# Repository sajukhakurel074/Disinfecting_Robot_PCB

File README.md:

# Disinfecting_Robot
Main circuit board design for disinfecting Robot Project.

This project was funded by Nepal Academy of Science and Technology (NAST) during the Covid-19 pandemic. The main aim of this project was to use a remotely comtrolled robot that would spary the disinfecting solution in the infected areas.

# Features of the board
1. Simple 4 wheel drive
2. Bluetooth controlled functions
3. Relay switched Water Pump
4. 2-D axis spraying arm 
  - Servo for y-axis
  - Stepper for x-axis
5. Proximity sensor at the edges to avoid collision

# Final Board After Assmebly

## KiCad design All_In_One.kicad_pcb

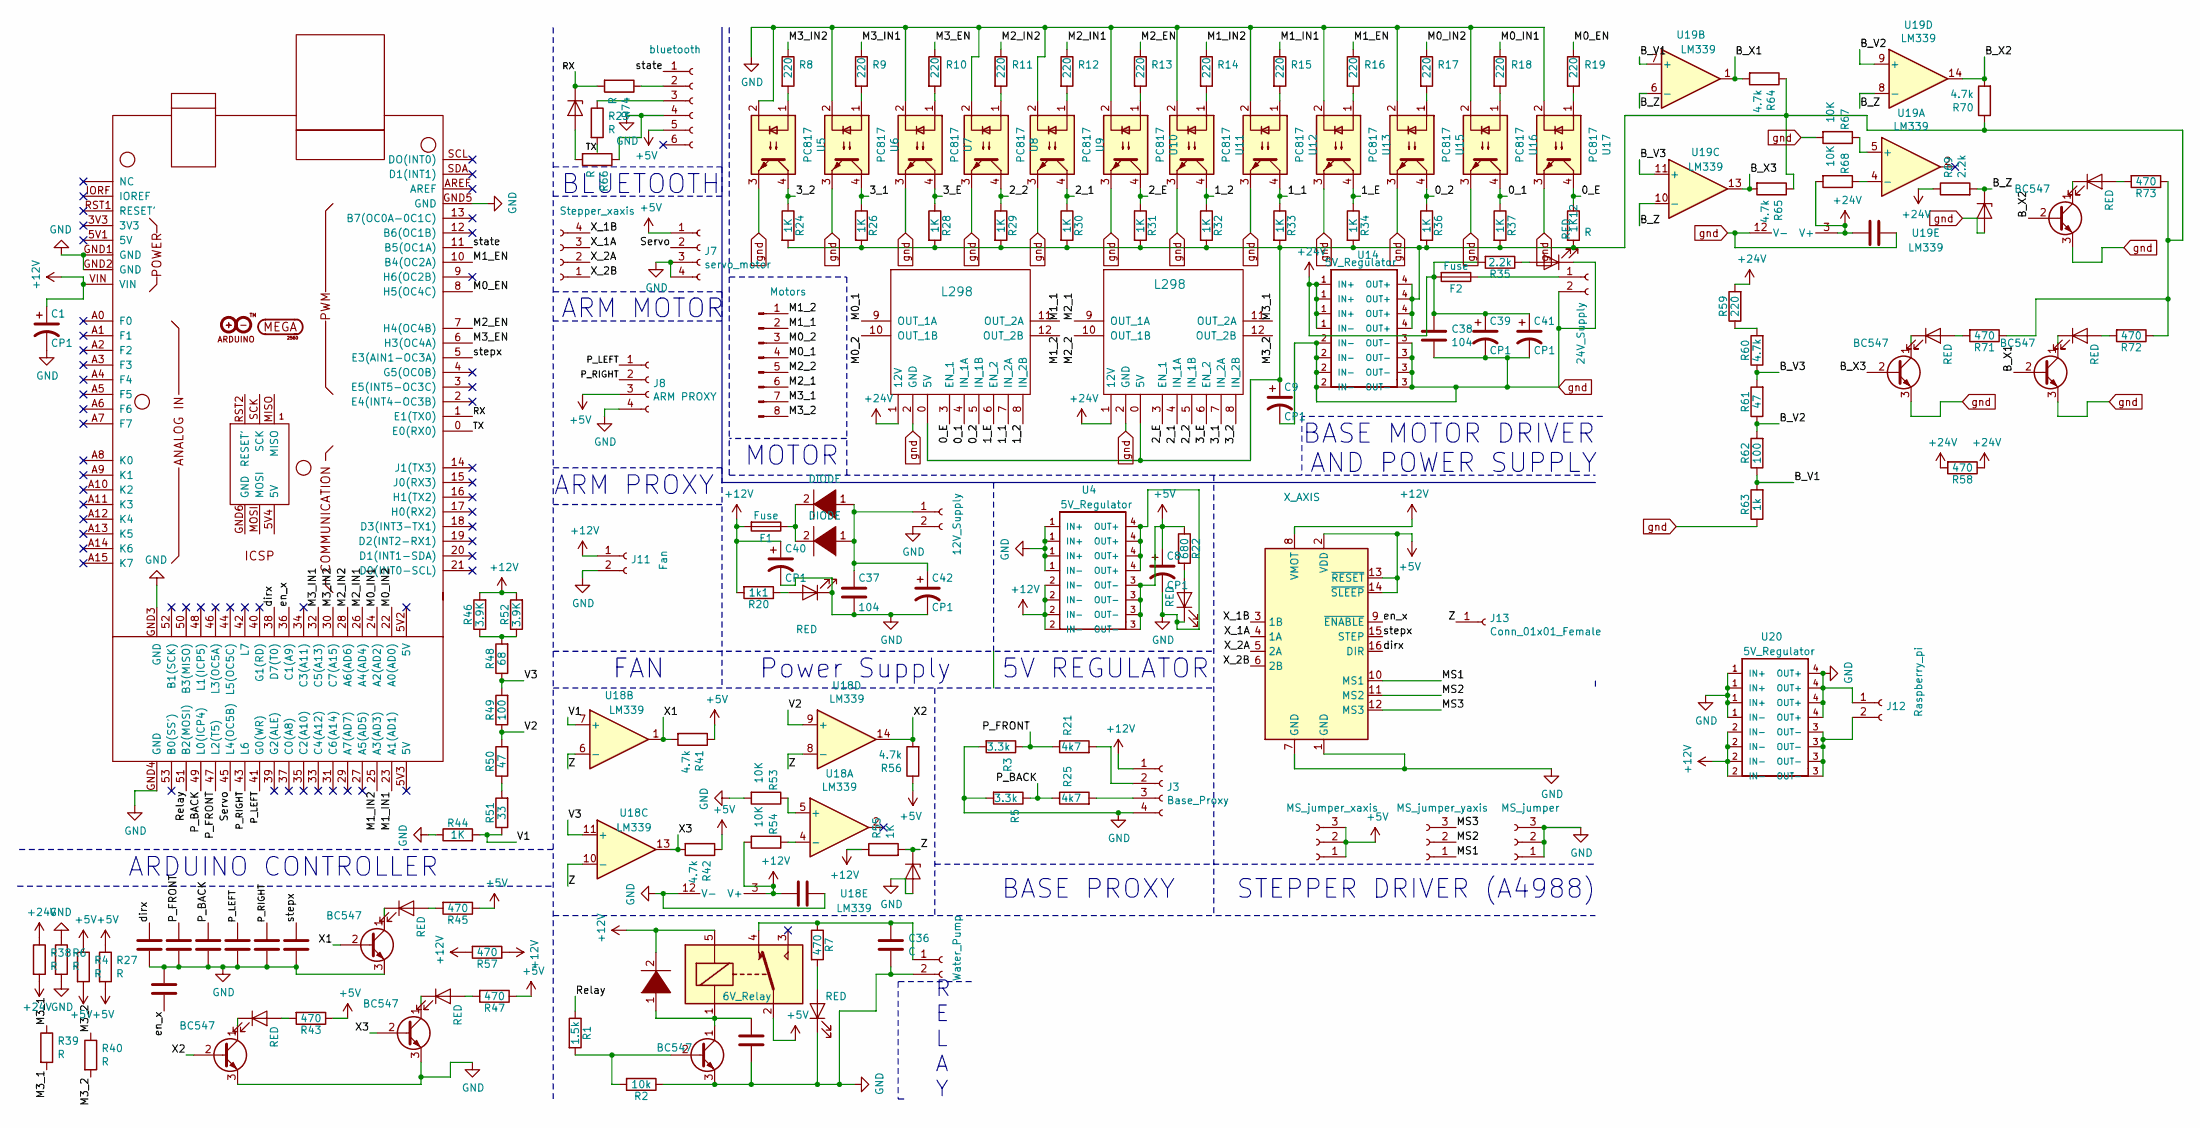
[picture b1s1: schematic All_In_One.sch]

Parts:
1K12: R; Resistor_small
A1: X_AXIS; A4998
C1, C8, C9, C40, C41: CP1; Capacitor_1000uF
C2, C3, C4, C5, C6, C7, C13, C25, C27, C33, C36: C; Capacitor_Disc_Small
C37, C38: 104; Capacitor_Disc_Small
C39, C42: CP1; Capacitor_10uF
D1, D3, D10: DIODE; Diode_Medium
D2, D4, D5, D6, D8, D9, D11, D13, D15, D16: RED; LED_D3.0mm
D7, D12, D14: D_Zener; D_T-1_P5.08mm_Horizontal
F1, F2: Fuse; Fuse_Holder
J1: MS_jumper_xaxis; PinHeader_1x03_P2.54mm_Vertical
J2: MS_jumper_yaxis; PinHeader_1x03_P2.54mm_Vertical
J3: Base_Proxy; New_conn_1x4
J4: Water_Pump; New_conn_1x2
J5: MS_jumper; PinHeader_1x03_P2.54mm_Vertical
J6: Stepper_xaxis; New_conn_1x4
J7: servo_motor; New_conn_1x4
J8: ARM PROXY; New_conn_1x4
J9: bluetooth
J10: Motors; New_conn_1x8
J11: Fan; New_conn_1x2
J12: Raspberry_pi; New_conn_1x2
J13: Conn_01x01_Female; PinHeader_1x01_P2.00mm_Vertical
Q1, Q2, Q3, Q4, Q5, Q6, Q7: BC547
R1: 1.5k; Resistor_small
R2: 10k; Resistor_small
R3, R5: 3.3k; Resistor_small
R4, R6, R23, R27, R38, R39, R40, R66, R74: R; Resistor_small
R7, R43, R45, R47, R57, R58, R71, R72, R73: 470; Resistor_small
R8, R9, R10, R11, R12, R13, R14, R15, R16, R17, R18, R19, R59: 220; Resistor_small
R20: 1k1; Resistor_small
R21, R25: 4k7; Resistor_small
R22: 680; Resistor_small
R24, R26, R28, R29, R30, R31, R32, R33, R34, R36, R37, R44, R55: 1K; Resistor_small
R35, R69: 2.2k; Resistor_small
R41, R42, R56, R60, R64, R65, R70: 4.7k; Resistor_small
R46, R52: 3.9K; Resistor_small
R48: 68; Resistor_small
R49, R62: 100; Resistor_small
R50, R61: 47; Resistor_small
R51: 33; Resistor_small
R53, R54, R67, R68: 10K; Resistor_small
R63: 1k; Resistor_small
Rly1: 6V_Relay; Relay_6V
U1: Prashant_library_Arduino_Mega2560_Shield; Arduino_Mega2560_Shield
U2, U3: L298; saju_____L298
U4, U20: 5V_Regulator; Buck_5A
U5, U6, U7, U8, U9, U10, U11, U12, U13, U15, U16, U17: PC817; DIP-4_W7.62mm
U14: 5V_Regulator; Buck_Regulator
U18, U19: LM339; DIP-14_W7.62mm_LongPads
d1: 12V_Supply; Solar_Connector
d2: 24V_Supply; Solar_Connector

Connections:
+5V: A1.2 (VDD), A1.13 (~RESET), A1.14 (~SLEEP), C8.1, J1.1, J1.2, J1.3, J7.1, J8.3, J9.5, R4.1, R4.2, R22.1, R27.1, R27.2, R41.1, R42.1, R43.1, R45.1, R47.1, R56.1, Rly1.2, U4.3 (OUT-); also elsewhere on the board
+12V: A1.8 (VMOT), C1.1, C4.2, C40.1, D1.2 (A), F1.2, J3.1, J11.1, R20.2, R46.2, R52.2, R54.2, R55.1, R57.1, R57.2, Rly1.5, U1.VIN, U4.2 (IN-), U18.3 (V+), U20.2 (IN-); also elsewhere on the board
+24V: C6.2, C38.1, C39.1, C41.1, F2.2, R35.2, R38.1, R38.2, R58.1, R58.2, R59.2, R68.2, R69.1, U2.1 (12V), U3.1 (12V), U14.1 (IN+), U19.3 (V+)
/0_1: R37.1, U2.4 (IN_1A), U16.4
/0_2: R36.1, U2.5 (IN_1B), U15.4
/0_E: 1K12.1, U2.3 (EN_1), U17.4
/1_1: R33.1, U2.7 (IN_2A), U12.4
/1_2: R32.1, U2.8 (IN_2B), U11.4
/1_E: R34.1, U2.6 (EN_2), U13.4
/2_1: R30.1, U3.4 (IN_1A), U9.4
/2_2: R29.1, U3.5 (IN_1B), U8.4
/2_E: R31.1, U3.3 (EN_1), U10.4
/3_1: R26.1, U3.7 (IN_2A), U6.4
/3_2: R24.1, U3.8 (IN_2B), U5.4
/3_E: R28.1, U3.6 (EN_2), U7.4
/B_V1: R62.1, R63.2, U19.7 (+)
/B_V2: R61.1, R62.2, U19.9 (+)
/B_V3: R60.1, R61.2, U19.11 (+)
/B_X1: Q6.2 (B), R64.2, U19.1
/B_X2: Q7.2 (B), R70.2, U19.14; also elsewhere on the board
/B_X3: Q5.2 (B), R65.2, U19.13
/B_Z: D14.1 (K), R69.2, U19.6 (-), U19.8 (-), U19.10 (-)
/M0_1: J10.4, U2.9 (OUT_1A)
/M0_2: J10.3, U2.10 (OUT_1B)
/M0_EN: R19.1, U1.8 (H5(OC4C))
/M0_IN1: R18.1, U1.24 (A2(AD2))
/M0_IN2: R17.1, U1.22 (A0(AD0))
/M1_1: J10.2, U2.11 (OUT_2A)
/M1_2: J10.1, U2.12 (OUT_2B)
/M1_EN: R16.1, U1.10 (B4(OC2A))
/M1_IN1: R15.1, U1.23 (A1(AD1))
/M1_IN2: R14.1, U1.25 (A3(AD3))
/M2_1: J10.6, U3.9 (OUT_1A)
/M2_2: J10.5, U3.10 (OUT_1B)
/M2_EN: R13.1, U1.7 (H4(OC4B))
/M2_IN1: R12.1, U1.26 (A4(AD4))
/M2_IN2: R11.1, U1.28 (A6(AD6))
/M3_1: J10.7, R39.1, R39.2, U3.11 (OUT_2A)
/M3_2: J10.8, R40.1, R40.2, U3.12 (OUT_2B)
/M3_EN: R10.1, U1.6 (H3(OC4A))
/M3_IN1: R9.1, U1.32 (C5(A13))
/M3_IN2: R8.1, U1.30 (C7(A15))
/MS1: A1.10 (MS1), J2.1; also elsewhere on the board
/MS2: A1.11 (MS2), J2.2; also elsewhere on the board
/MS3: A1.12 (MS3), J2.3; also elsewhere on the board
/P_BACK: C5.1, R5.1, R25.1, U1.49 (L0(ICP4))
/P_FRONT: C2.1, R3.1, R21.1, U1.47 (L2(T5))
/P_LEFT: C25.1, J8.1, U1.41 (G0(WR))
/P_RIGHT: C27.1, J8.2, U1.43 (L6)
/RX: D7.1 (K), R74.2, U1.1 (E1(TX0))
/Relay: R1.1, U1.51 (B2(MOSI))
/Servo: J7.2, U1.45 (L4(OC5B))
/TX: R23.2, U1.0 (E0(RX0))
/V1: R44.2, R51.1, U18.7 (+)
/V2: R49.1, R50.2, U18.9 (+)
/V3: R48.1, R49.2, U18.11 (+)
/X1: Q3.2 (B), R41.2, U18.1
/X2: Q2.2 (B), R56.2, U18.14
/X3: Q4.2 (B), R42.2, U18.13
/X_1A: A1.4 (1A), J6.3
/X_1B: A1.3 (1B), J6.4
/X_2A: A1.5 (2A), J6.2
/X_2B: A1.6 (2B), J6.1
/Z: D12.1 (K), J13.1, R55.2, U18.6 (-), U18.8 (-), U18.10 (-); also elsewhere on the board
/dirx: A1.16 (DIR), C13.1, U1.38 (D7(T0))
/en_x: A1.9 (~ENABLE), C3.1, U1.36 (C1(A9))
/state: J9.1, U1.11 (B5(OC1A))
/stepx: A1.15 (STEP), C33.1, U1.5 (E3(AIN1-OC3A))
GND: A1.1 (GND), A1.7 (GND), C1.2, C2.2, C3.2, C4.1, C5.2, C7.2, C8.2, C13.2, C25.2, C27.2, C33.2, C36.2, C37.2, C40.2, C42.2, D2.1 (K), D9.1 (K), D11.1 (K), D12.2 (A), J3.4, J4.2, J5.1, J5.2, J5.3, J7.3, J7.4, J8.4, J9.4, J11.2, J12.1, Q1.3 (E), Q2.3 (E), Q3.3 (E), Q4.3 (E), R2.1, R3.2, R5.2, R6.1, R6.2, R44.1, R53.2, R66.1, U1.GND1 (GND), U1.GND2 (GND), U1.GND3 (GND), U1.GND4 (GND), U1.GND5 (GND), U4.1 (IN+), U4.4 (OUT+), U5.2, U6.2, U7.2, U8.2, U9.2, U10.2, U11.2, U12.2, U13.2, U15.2, U16.2, U17.2, U18.12 (V-), U20.1 (IN+), U20.4 (OUT+), d1.2; also elsewhere on the board
unnamed 69: 1K12.2, C9.1, R24.2, R26.2, R28.2, R29.2, R30.2, R31.2, R32.2, R33.2, R34.2, R36.2, R37.2, R64.1, R65.1, R70.1, R71.1, R72.1, R73.1, U2.0 (5V), U3.0 (5V), U14.4 (OUT+); also elsewhere on the board
unnamed: C7.1, D1.1 (K), Q1.1 (C), Rly1.1
unnamed: C36.1, J4.1, R7.1, Rly1.4
unnamed 72: C37.1, C42.1, D3.1 (K), D10.1 (K), d1.1; also elsewhere on the board
unnamed: D2.2 (A), R7.2
unnamed: D4.1 (K), Q2.1 (C)
unnamed: D4.2 (A), R43.2
unnamed: D5.1 (K), Q3.1 (C)
unnamed: D5.2 (A), R45.2
unnamed: D6.1 (K), Q4.1 (C)
unnamed: D6.2 (A), R47.2
unnamed: D7.2 (A), R66.2
unnamed: D8.2 (A), R35.1
unnamed: D9.2 (A), R20.1
unnamed: D3.2 (A), D10.2 (A), F1.1
unnamed: D11.2 (A), R22.2
unnamed: D13.1 (K), Q5.1 (C)
unnamed: D13.2 (A), R71.2
unnamed: D15.1 (K), Q6.1 (C)
unnamed: D15.2 (A), R72.2
unnamed: D16.1 (K), Q7.1 (C)
unnamed: D16.2 (A), R73.2
unnamed: F2.1, d2.1
unnamed: J3.2, R21.2
unnamed: J3.3, R25.2
unnamed: J9.2, R74.1
unnamed: J9.3, R23.1
unnamed: J12.2, U20.3 (OUT-)
unnamed: Q1.2 (B), R1.2, R2.2
unnamed: R8.2, U5.1
unnamed: R9.2, U6.1
unnamed: R10.2, U7.1
unnamed: R11.2, U8.1
unnamed: R12.2, U9.1
unnamed: R13.2, U10.1
unnamed: R14.2, U11.1
unnamed: R15.2, U12.1
unnamed: R16.2, U13.1
unnamed: R17.2, U15.1
unnamed: R18.2, U16.1
unnamed: R19.2, U17.1
unnamed: R46.1, R48.2, R52.1
unnamed: R50.1, R51.2
unnamed: R53.1, U18.5 (+)
unnamed: R54.1, U18.4 (-)
unnamed: R59.1, R60.2
unnamed: R67.1, U19.5 (+)
unnamed: R68.1, U19.4 (-)
gnd: C6.1, C9.2, C38.2, C39.2, C41.2, D8.1 (K), D14.2 (A), Q5.3 (E), Q6.3 (E), Q7.3 (E), R63.1, R67.2, U2.2 (GND), U3.2 (GND), U5.3, U6.3, U7.3, U8.3, U9.3, U10.3, U11.3, U12.3, U13.3, U14.2 (IN-), U14.3 (OUT-), U15.3, U16.3, U17.3, U19.12 (V-), d2.2

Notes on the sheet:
ARM PROXY
5V REGULATOR
ARDUINO CONTROLLER
MOTOR
BASE PROXY
STEPPER DRIVER (A4988)
BASE MOTOR DRIVER
AND POWER SUPPLY
Power Supply
BLUETOOTH
R E L A Y
FAN
ARM MOTOR

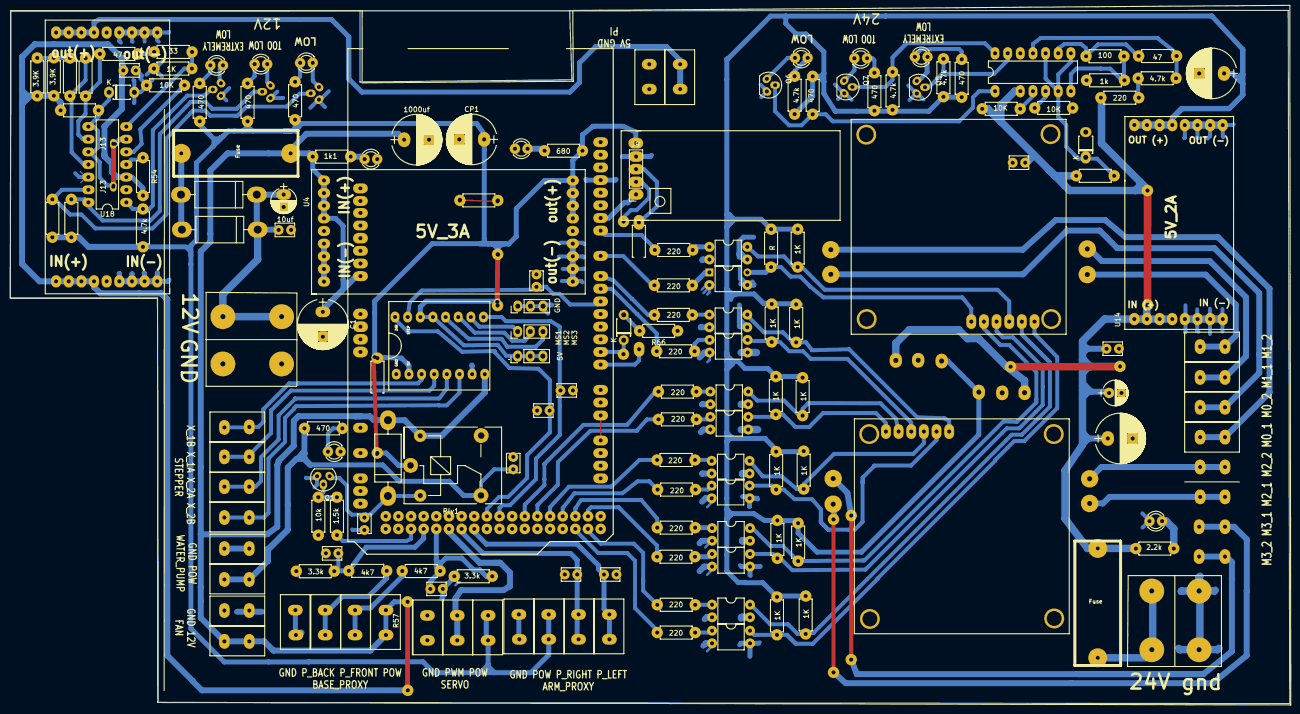
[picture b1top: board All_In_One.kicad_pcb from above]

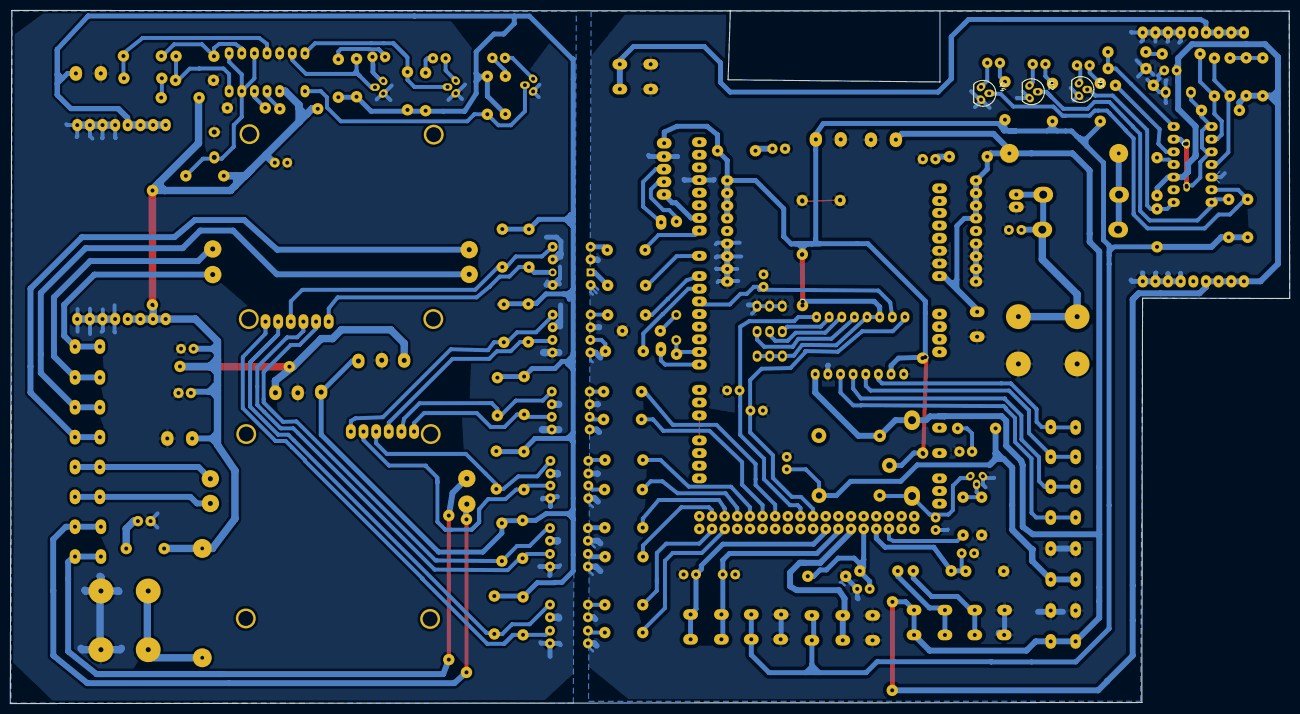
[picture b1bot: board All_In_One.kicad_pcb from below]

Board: 2 copper layers, 257.1 x 139.3 mm, 158 parts (3 on the bottom side), 118 nets.

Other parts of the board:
5V: MS_jumper_xaxis; PinHeader_1x03_P2.54mm_Vertical
10uf: CP1; Capacitor_10uF
1000uf: CP1; Capacitor_1000uF
GND: MS_jumper; PinHeader_1x03_P2.54mm_Vertical
J13#2: Conn_01x01_Female; PinHeader_1x01_P2.00mm_Vertical
MS1: MS_jumper_yaxis; PinHeader_1x03_P2.54mm_Vertical
eR70: 4.7k; Resistor_small

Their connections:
+5V: 5V.1, 5V.2, 5V.3; also elsewhere on the board
+12V: 1000uf.1; also elsewhere on the board
/B_X2: eR70.2; also elsewhere on the board
/MS1: MS1.1; also elsewhere on the board
/MS2: MS1.2; also elsewhere on the board
/MS3: MS1.3; also elsewhere on the board
/Z: J13#2.1; also elsewhere on the board
GND: 10uf.2, 1000uf.2, GND.1, GND.2, GND.3; also elsewhere on the board
unnamed 69: eR70.1; also elsewhere on the board
unnamed 72: 10uf.1; also elsewhere on the board

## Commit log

2020-07-27 sechematic
2020-08-05 complete schematic
2020-08-09 seperate ground for base motor and rest using opto-coupler
2020-08-14 started joining tracks
2020-08-15 completed joining tracks!
2020-08-16 completed circuit
2020-08-17 completed circuit1
2020-08-18 battery indicator
2020-08-18 added buck for pi
2020-08-20 completed board!
2020-09-29 finalized board
2023-04-16 Add Readme
2023-04-17 Update Read me
